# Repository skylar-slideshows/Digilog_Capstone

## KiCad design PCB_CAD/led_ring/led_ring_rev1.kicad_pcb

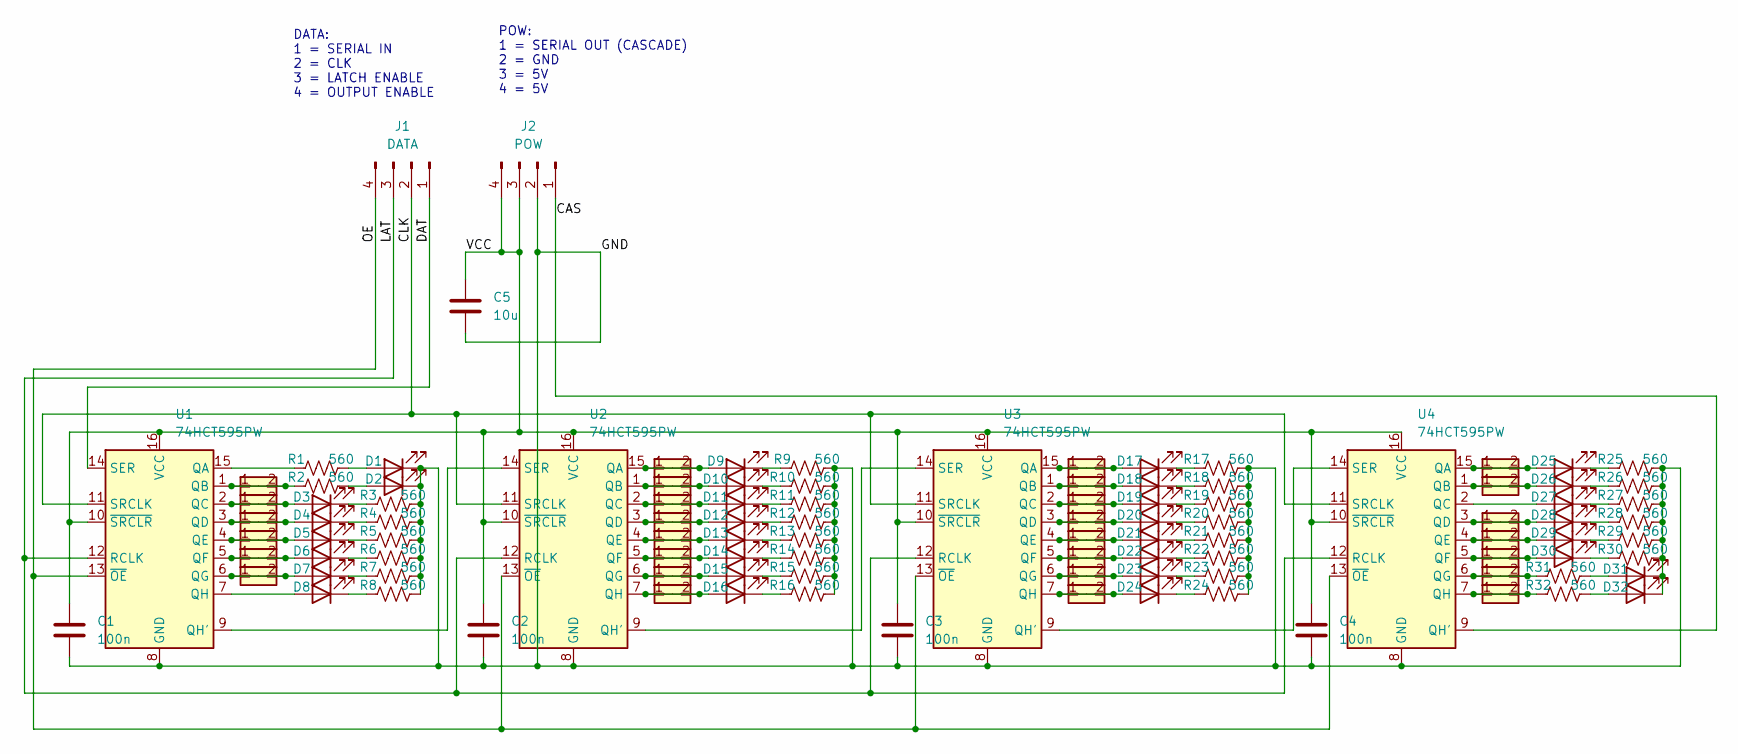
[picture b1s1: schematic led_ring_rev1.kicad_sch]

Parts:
C1, C2, C3, C4: 100n; C_0402_1005Metric; LCSC C1525
C5: 10u; C_0402_1005Metric; LCSC C386033
D1, D2, D3, D4, D5, D6, D7, D8, D9, D10, D11, D12, D13, D14, D15, D16, D17, D18, D19, D20, D21, D22, D23, D24, D25, D26, D27, D28, D29, D30, D31, D32: LED; LED_0201_0603Metric; LCSC C52675959
J1: DATA; PinHeader_1x04_P2.54mm_Vertical; LCSC C5116483
J2: POW; PinHeader_1x04_P2.54mm_Vertical; LCSC C5116483
R1, R2, R3, R4, R5, R6, R7, R8, R9, R10, R11, R12, R13, R14, R15, R16, R17, R18, R19, R20, R21, R22, R23, R24, R25, R26, R27, R28, R29, R30, R31, R32: 560; R_0201_0603Metric; LCSC C295808
U1, U2, U3, U4: 74HCT595PW; TSSOP-16_4.4x5mm_P0.65mm; LCSC C54411086
V2, V3, V4, V5, V6, V7, V9, V10, V11, V12, V13, V14, V15, V16, V17, V18, V19, V20, V21, V22, V23, V24, V25, V26, V28, V29, V30, V31, V32: VIA; VIA_0.5_0.3

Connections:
/CAS: J2.1, U4.9 (QH')
/CLK: J1.2, U1.11 (SRCLK), U2.11 (SRCLK), U3.11 (SRCLK), U4.11 (SRCLK)
/DAT: J1.1, U1.14 (SER)
/GND: C1.2, C2.2, C3.2, C4.2, C5.2, D1.1 (K), D2.1 (K), D31.1 (K), D32.1 (K), J2.2, R3.2, R4.2, R5.2, R6.2, R7.2, R8.2, R9.2, R10.2, R11.2, R12.2, R13.2, R14.2, R15.2, R16.2, R17.2, R18.2, R19.2, R20.2, R21.2, R22.2, R23.2, R24.2, R25.2, R26.2, R27.2, R28.2, R29.2, R30.2, U1.8 (GND), U2.8 (GND), U3.8 (GND), U4.8 (GND)
/LAT: J1.3, U1.12 (RCLK), U2.12 (RCLK), U3.12 (RCLK), U4.12 (RCLK)
/OE: J1.4, U1.13 (~OE), U2.13 (~OE), U3.13 (~OE), U4.13 (~OE)
/VCC: C1.1, C2.1, C3.1, C4.1, C5.1, J2.3, J2.4, U1.10 (~SRCLR), U1.16 (VCC), U2.10 (~SRCLR), U2.16 (VCC), U3.10 (~SRCLR), U3.16 (VCC), U4.10 (~SRCLR), U4.16 (VCC)
unnamed: D1.2 (A), R1.2
unnamed: D2.2 (A), R2.2
unnamed: D3.2 (A), U1.2 (QC), V3.1, V3.2
unnamed: D3.1 (K), R3.1
unnamed: D4.2 (A), U1.3 (QD), V4.1, V4.2
unnamed: D4.1 (K), R4.1
unnamed: D5.2 (A), U1.4 (QE), V5.1, V5.2
unnamed: D5.1 (K), R5.1
unnamed: D6.2 (A), U1.5 (QF), V6.1, V6.2
unnamed: D6.1 (K), R6.1
unnamed: D7.2 (A), U1.6 (QG), V7.1, V7.2
unnamed: D7.1 (K), R7.1
unnamed: D8.2 (A), U1.7 (QH)
unnamed: D8.1 (K), R8.1
unnamed: D9.2 (A), U2.15 (QA), V9.1, V9.2
unnamed: D9.1 (K), R9.1
unnamed: D10.2 (A), U2.1 (QB), V10.1, V10.2
unnamed: D10.1 (K), R10.1
unnamed: D11.2 (A), U2.2 (QC), V11.1, V11.2
unnamed: D11.1 (K), R11.1
unnamed: D12.2 (A), U2.3 (QD), V12.1, V12.2
unnamed: D12.1 (K), R12.1
unnamed: D13.2 (A), U2.4 (QE), V13.1, V13.2
unnamed: D13.1 (K), R13.1
unnamed: D14.2 (A), U2.5 (QF), V14.1, V14.2
unnamed: D14.1 (K), R14.1
unnamed: D15.2 (A), U2.6 (QG), V15.1, V15.2
unnamed: D15.1 (K), R15.1
unnamed: D16.2 (A), U2.7 (QH), V16.1, V16.2
unnamed: D16.1 (K), R16.1
unnamed: D17.2 (A), U3.15 (QA), V17.1, V17.2
unnamed: D17.1 (K), R17.1
unnamed: D18.2 (A), U3.1 (QB), V18.1, V18.2
unnamed: D18.1 (K), R18.1
unnamed: D19.2 (A), U3.2 (QC), V19.1, V19.2
unnamed: D19.1 (K), R19.1
unnamed: D20.2 (A), U3.3 (QD), V20.1, V20.2
unnamed: D20.1 (K), R20.1
unnamed: D21.2 (A), U3.4 (QE), V21.1, V21.2
unnamed: D21.1 (K), R21.1
unnamed: D22.2 (A), U3.5 (QF), V22.1, V22.2
unnamed: D22.1 (K), R22.1
unnamed: D23.2 (A), U3.6 (QG), V23.1, V23.2
unnamed: D23.1 (K), R23.1
unnamed: D24.2 (A), U3.7 (QH), V24.1, V24.2
unnamed: D24.1 (K), R24.1
unnamed: D25.2 (A), U4.15 (QA), V25.1, V25.2
unnamed: D25.1 (K), R25.1
unnamed: D26.2 (A), U4.1 (QB), V26.1, V26.2
unnamed: D26.1 (K), R26.1
unnamed: D27.2 (A), U4.2 (QC)
unnamed: D27.1 (K), R27.1
unnamed: D28.2 (A), U4.3 (QD), V28.1, V28.2
unnamed: D28.1 (K), R28.1
unnamed: D29.2 (A), U4.4 (QE), V29.1, V29.2
unnamed: D29.1 (K), R29.1
unnamed: D30.2 (A), U4.5 (QF), V30.1, V30.2
unnamed: D30.1 (K), R30.1
unnamed: D31.2 (A), R31.2
unnamed: D32.2 (A), R32.2
unnamed: R1.1, U1.15 (QA)
unnamed: R2.1, U1.1 (QB), V2.1, V2.2
unnamed: U1.9 (QH'), U2.14 (SER)
unnamed: U2.9 (QH'), U3.14 (SER)
unnamed: U3.9 (QH'), U4.14 (SER)
unnamed: R31.1, U4.6 (QG), V31.1, V31.2
unnamed: R32.1, U4.7 (QH), V32.1, V32.2

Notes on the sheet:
DATA: 1 = SERIAL IN 2 = CLK 3 = LATCH ENABLE 4 = OUTPUT ENABLE
POW: 1 = SERIAL OUT (CASCADE) 2 = GND 3 = 5V 4 = 5V

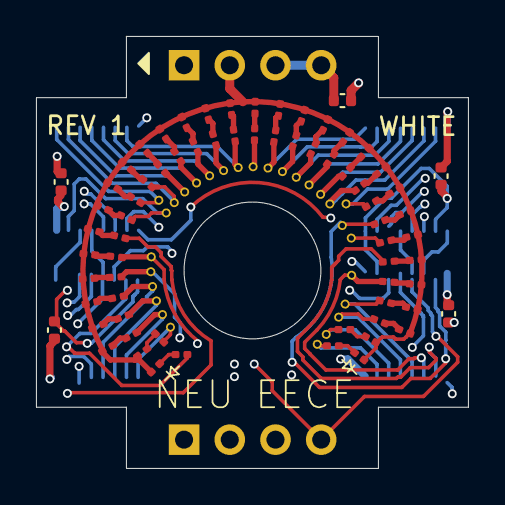
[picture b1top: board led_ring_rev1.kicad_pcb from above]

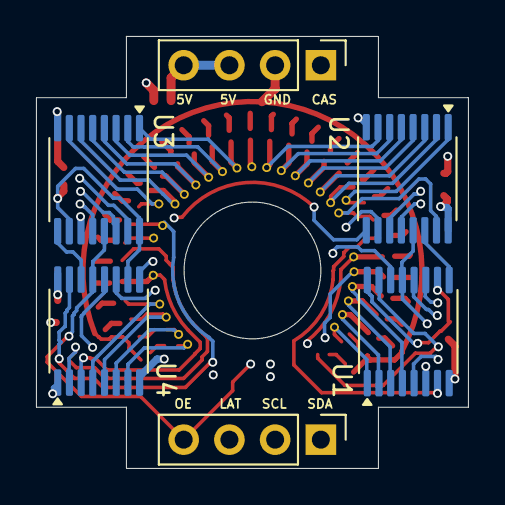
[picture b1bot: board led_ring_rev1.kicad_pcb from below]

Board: 4 copper layers, 24.0 x 24.0 mm, 104 parts (6 on the bottom side), 74 nets.

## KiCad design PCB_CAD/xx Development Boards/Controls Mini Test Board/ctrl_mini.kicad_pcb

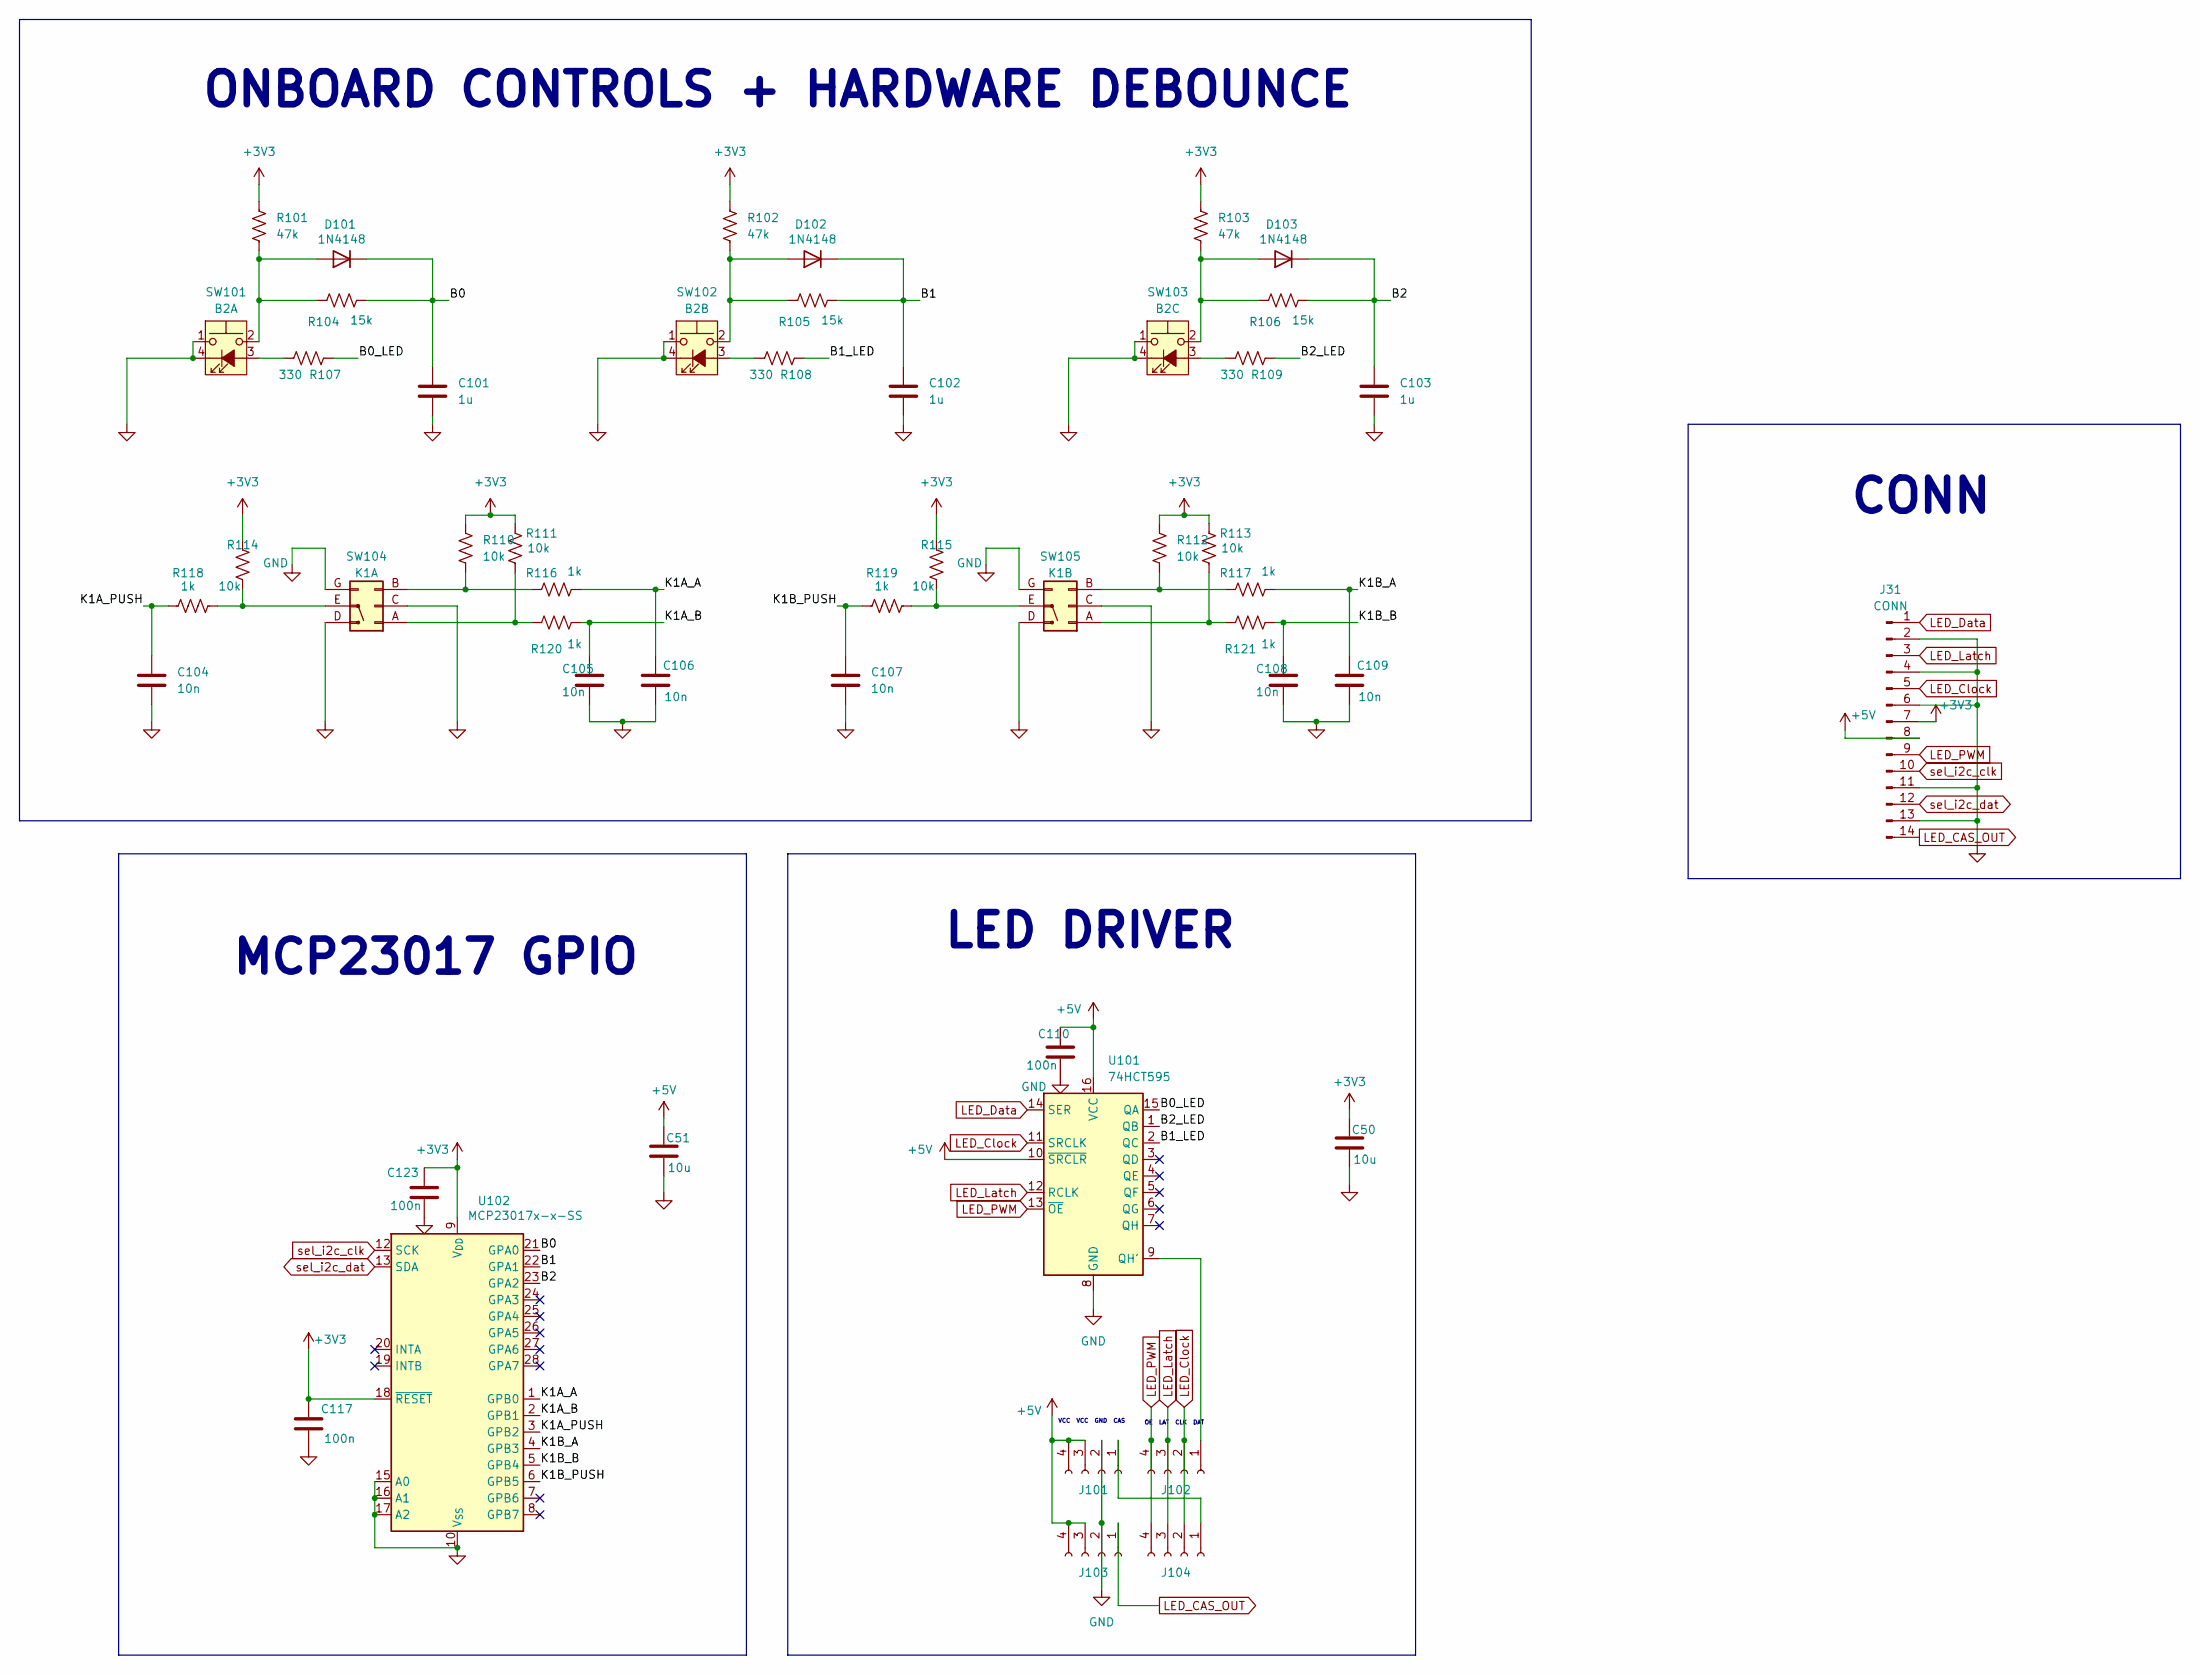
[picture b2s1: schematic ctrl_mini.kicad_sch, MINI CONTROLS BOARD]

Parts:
C50, C51: 10u; C_1206_3216Metric; LCSC C1849
C101, C102, C103: 1u; C_0603_1608Metric; LCSC C1592
C104, C105, C106, C107, C108, C109: 10n; C_0603_1608Metric; LCSC C57112
C110, C117, C123: 100n; C_0603_1608Metric; LCSC C1590
D101, D102, D103: 1N4148; D_SOD-323; LCSC C2128
J31: CONN; PinHeader_1x14_P2.54mm_Vertical
J101, J102, J103, J104: Conn_01x04_Socket; PinSocket_1x04_P2.54mm_Vertical
R101, R102, R103: 47k; R_0603_1608Metric; LCSC C25819
R104, R105, R106: 15k; R_0603_1608Metric; LCSC C22809
R107, R108, R109: 330; R_0603_1608Metric; LCSC C23138
R110, R111, R112, R113, R114, R115: 10k; R_0603_1608Metric; LCSC C25804
R116, R117, R118, R119, R120, R121: 1k; R_0603_1608Metric; LCSC C21190
SW101: B2A; CFPB-1CC-4W6
SW102: B2B; CFPB-1CC-4W6
SW103: B2C; CFPB-1CC-4W6
SW104: K1A; EC11J0924411
SW105: K1B; EC11J0924411
U101: 74HCT595; SOIC-16_3.9x9.9mm_P1.27mm; LCSC C282339
U102: MCP23017x-x-SS; SSOP-28_5.3x10.2mm_P0.65mm; LCSC C506653

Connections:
+3V3: C50.1, C117.1, C123.1, J31.7, R101.1, R102.1, R103.1, R110.1, R111.1, R112.1, R113.1, R114.1, R115.1, U102.9 (V_{DD}), U102.18 (~RESET)
+5V: C51.1, C110.1, J31.8, J101.3, J101.4, J103.3, J103.4, U101.10 (~SRCLR), U101.16 (VCC)
/B0: C101.1, D101.1 (K), R104.2, U102.21 (GPA0)
/B0_LED: R107.2, U101.15 (QA)
/B1: C102.1, D102.1 (K), R105.2, U102.22 (GPA1)
/B1_LED: R108.2, U101.2 (QC)
/B2: C103.1, D103.1 (K), R106.2, U102.23 (GPA2)
/B2_LED: R109.2, U101.1 (QB)
/K1A_A: C106.1, R116.2, U102.1 (GPB0)
/K1A_B: C105.1, R120.2, U102.2 (GPB1)
/K1A_PUSH: C104.1, R118.1, U102.3 (GPB2)
/K1B_A: C109.1, R117.2, U102.4 (GPB3)
/K1B_B: C108.1, R121.2, U102.5 (GPB4)
/K1B_PUSH: C107.1, R119.1, U102.6 (GPB5)
GND: C50.2, C51.2, C101.2, C102.2, C103.2, C104.2, C105.2, C106.2, C107.2, C108.2, C109.2, C110.2, C117.2, C123.2, J31.2, J31.4, J31.6, J31.11, J31.13, J101.2, J103.2, SW101.1, SW101.4 (K), SW102.1, SW102.4 (K), SW103.1, SW103.4 (K), SW104.C (Pin_2), SW104.D (Pin_4), SW104.G (Pin_6), SW105.C (Pin_2), SW105.D (Pin_4), SW105.G (Pin_6), U101.8 (GND), U102.10 (V_{SS}), U102.15 (A0), U102.16 (A1), U102.17 (A2)
LED_CAS_OUT: J31.14, J103.1
LED_Clock: J31.5, J102.2, J104.2, U101.11 (SRCLK)
LED_Data: J31.1, U101.14 (SER)
LED_Latch: J31.3, J102.3, J104.3, U101.12 (RCLK)
LED_PWM: J31.9, J102.4, J104.4, U101.13 (~OE)
unnamed: D101.2 (A), R101.2, R104.1, SW101.2
unnamed: D102.2 (A), R102.2, R105.1, SW102.2
unnamed: D103.2 (A), R103.2, R106.1, SW103.2
unnamed: J101.1, J104.1
unnamed: J102.1, U101.9 (QH')
unnamed: R107.1, SW101.3 (A)
unnamed: R108.1, SW102.3 (A)
unnamed: R109.1, SW103.3 (A)
unnamed: R111.2, R120.1, SW104.A (Pin_1)
unnamed: R110.2, R116.1, SW104.B (Pin_3)
unnamed: R114.2, R118.2, SW104.E (Pin_5)
unnamed: R113.2, R121.1, SW105.A (Pin_1)
unnamed: R112.2, R117.1, SW105.B (Pin_3)
unnamed: R115.2, R119.2, SW105.E (Pin_5)
sel_i2c_clk: J31.10, U102.12 (SCK)
sel_i2c_dat: J31.12, U102.13 (SDA)

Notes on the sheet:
ONBOARD CONTROLS + HARDWARE DEBOUNCE
VCC VCC GND CAS
OE LAT CLK DAT
CONN
LED DRIVER
MCP23017 GPIO

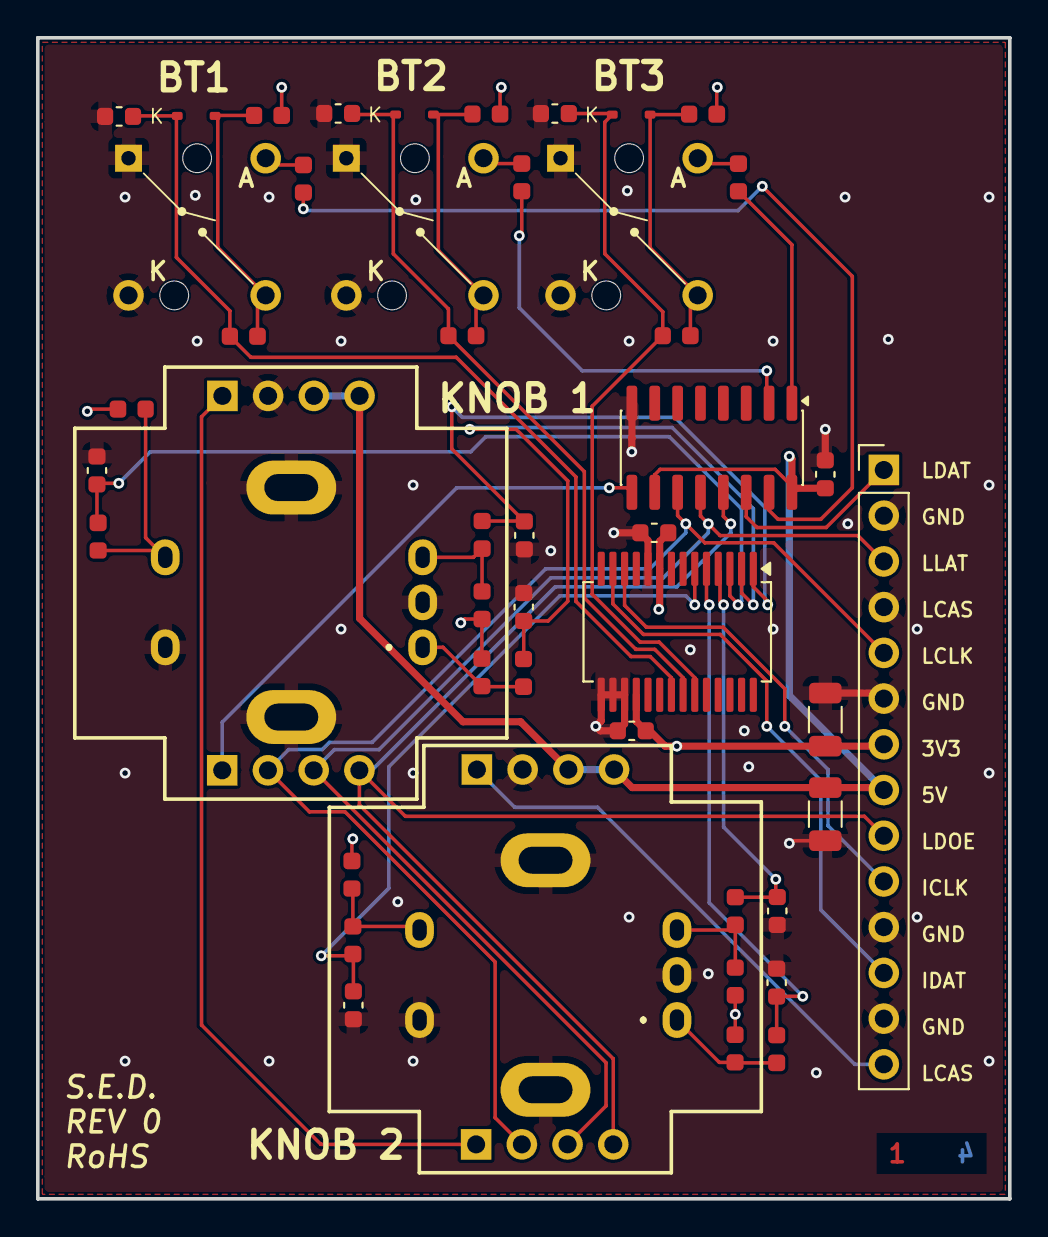
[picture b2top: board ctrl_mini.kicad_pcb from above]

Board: 4 copper layers, 54.0 x 64.5 mm, 50 parts (0 on the bottom side), 36 nets.

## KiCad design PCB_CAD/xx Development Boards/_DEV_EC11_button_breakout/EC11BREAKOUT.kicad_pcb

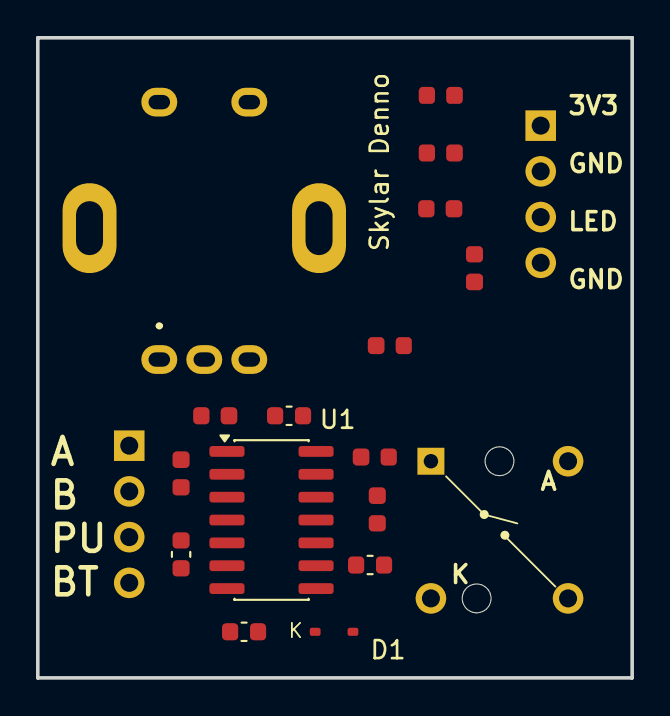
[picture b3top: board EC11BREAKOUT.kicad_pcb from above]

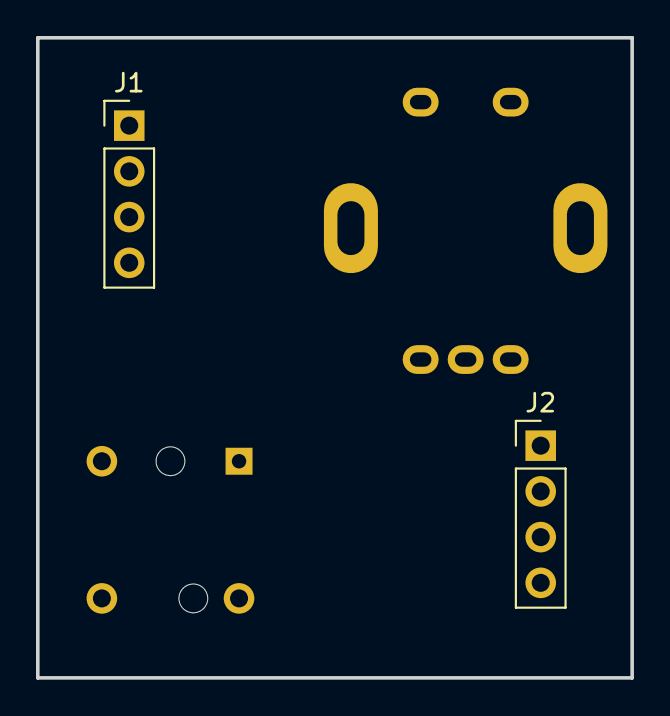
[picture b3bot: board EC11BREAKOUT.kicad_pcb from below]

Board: 4 copper layers, 33.0 x 35.6 mm, 19 parts (2 on the bottom side), 16 nets, no tracks yet.

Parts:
C1: 1u; C_0603_1608Metric
C2, C3, C4: 10n; C_0603_1608Metric
D1: 1N4148; D_SOD-323
J1, J2: Conn_01x04_Pin; PinHeader_1x04_P2.54mm_Vertical
R1: 47k; R_0603_1608Metric
R2: 15k; R_0603_1608Metric
R3, R4, R5: 10k; R_0603_1608Metric
R6, R7, R8: 1k; R_0603_1608Metric
R9: 330; R_0603_1608Metric
SW1: EC11_Rotary_Encoder; EC11J0924411
SW2: SW_Push_LED; CFPB-1CC-4W6
U1: 74HC14; SOIC-14_3.9x8.7mm_P1.27mm

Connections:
+3V3: J1.1, R1.1, R3.1, R4.1, R5.1, U1.14 (VCC)
GND: C1.2, C2.2, C3.2, C4.2, J1.2, J1.4, SW1.C (Pin_2), SW1.D (Pin_4), SW1.G (Pin_6), SW2.1, SW2.4 (K), U1.7 (GND)
KNOB_A: J2.1, U1.4
KNOB_B: J2.2, U1.6
KNOB_SW: J2.3, U1.2
LED: J1.3, R9.2
unnamed: C2.1, R6.1, U1.1
unnamed: C3.1, R7.2, U1.5
unnamed: C4.1, R8.2, U1.3
unnamed: D1.2 (A), R1.2, R2.1, SW2.2
unnamed: C1.1, D1.1 (K), R2.2, U1.9
unnamed: R5.2, R7.1, SW1.A (Pin_1)
unnamed: R4.2, R8.1, SW1.B (Pin_3)
unnamed: R3.2, R6.2, SW1.E (Pin_5)
unnamed: R9.1, SW2.3 (A)
SW: J2.4, U1.8

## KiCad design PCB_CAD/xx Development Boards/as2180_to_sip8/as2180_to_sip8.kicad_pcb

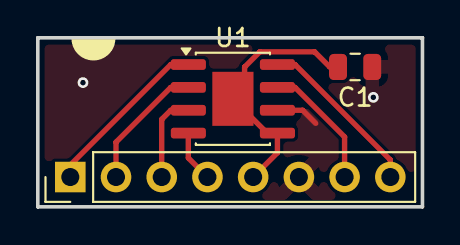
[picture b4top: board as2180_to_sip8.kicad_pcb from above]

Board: 2 copper layers, 21.4 x 9.4 mm, 3 parts (0 on the bottom side), 8 nets.

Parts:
C1: 100n; C_0805_2012Metric
J1: Conn_01x08_Pin; PinHeader_1x08_P2.54mm_Vertical
U1: AS2180; SOIC-8-1EP_3.9x4.9mm_P1.27mm_EP2.29x3mm

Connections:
unnamed: J1.1, U1.1 (-)
unnamed: J1.2, U1.2 (E+)
unnamed: J1.3, U1.3 (E-)
unnamed: J1.4, U1.4 (SYM)
unnamed: C1.2, J1.5, U1.5 (V-), U1.9 (EP)
unnamed: C1.1, J1.6, U1.6 (GND)
unnamed: J1.7, U1.7 (V+)
unnamed: J1.8, U1.8
